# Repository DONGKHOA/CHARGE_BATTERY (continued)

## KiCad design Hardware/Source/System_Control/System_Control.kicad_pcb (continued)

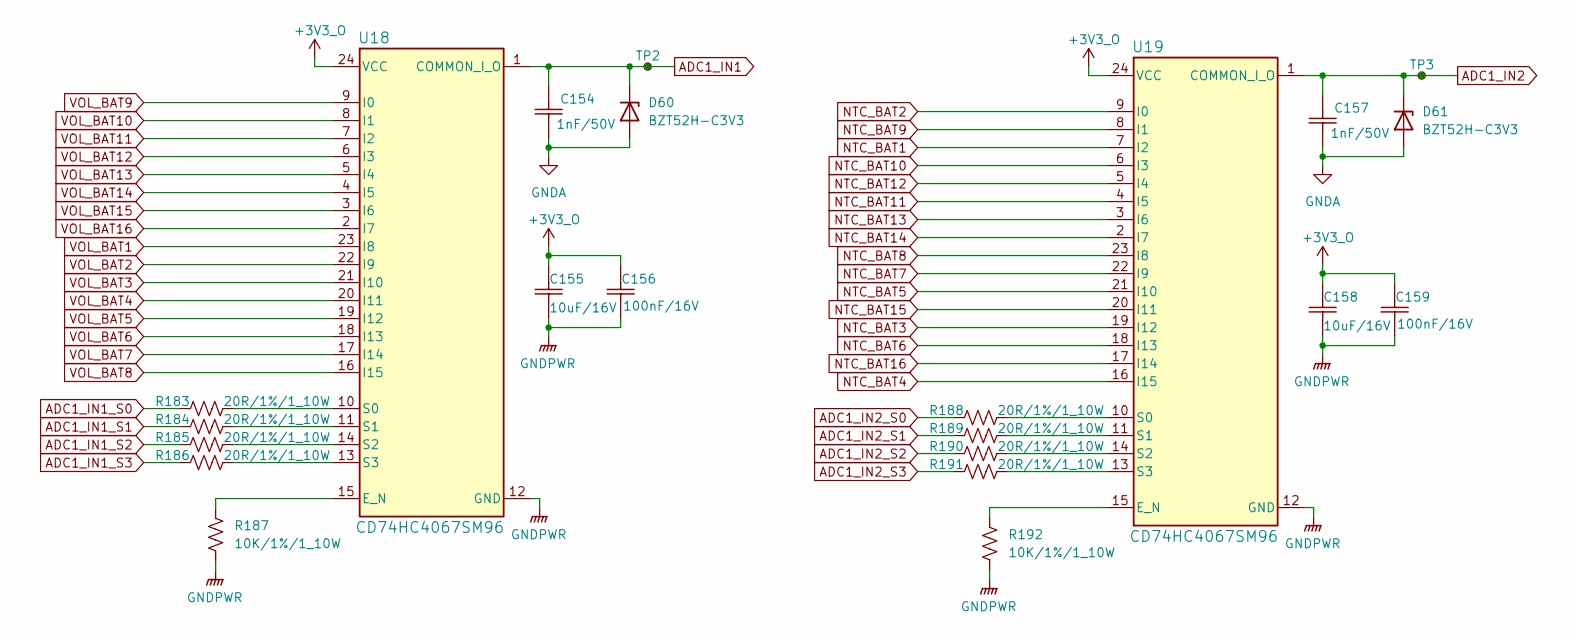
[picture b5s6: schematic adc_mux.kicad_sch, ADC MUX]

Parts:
C154, C157: 1nF/50V; Ceramic_Cap_0603
C155, C158: 10uF/16V; Ceramic_Cap_0603
C156, C159: 100nF/16V; Ceramic_Cap_0603
D60, D61: BZT52H-C3V3; Diode_Zener_BZT52H
R183, R184, R185, R186, R188, R189, R190, R191: 20R/1%/1_10W; Res_0603
R187, R192: 10K/1%/1_10W; Res_0603
TP2, TP3: TestPoint_Small; TestPoint_Pad_D1.0mm
U18, U19: CD74HC4067SM96; SOIC-24

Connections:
+3V3_O: C155.2, C156.2, C158.2, C159.2, U18.24 (VCC), U19.24 (VCC); also elsewhere on the board
ADC1_IN1: C154.2, D60.1 (K), TP2.1, U18.1 (COMMON_I_O); also elsewhere on the board
ADC1_IN1_S0: R183.1; also elsewhere on the board
ADC1_IN1_S1: R184.1; also elsewhere on the board
ADC1_IN1_S2: R185.1; also elsewhere on the board
ADC1_IN1_S3: R186.1; also elsewhere on the board
ADC1_IN2: C157.2, D61.1 (K), TP3.1, U19.1 (COMMON_I_O); also elsewhere on the board
ADC1_IN2_S0: R188.1; also elsewhere on the board
ADC1_IN2_S1: R189.1; also elsewhere on the board
ADC1_IN2_S2: R190.1; also elsewhere on the board
ADC1_IN2_S3: R191.1; also elsewhere on the board
GNDA: C154.1, C155.1, C156.1, C157.1, C158.1, C159.1, D60.2 (A), D61.2 (A), R187.1, R192.1, U18.12 (GND), U19.12 (GND); also elsewhere on the board
NTC_BAT1: U19.7 (I2); also elsewhere on the board
NTC_BAT2: U19.9 (I0); also elsewhere on the board
NTC_BAT3: U19.19 (I12); also elsewhere on the board
NTC_BAT4: U19.16 (I15); also elsewhere on the board
NTC_BAT5: U19.21 (I10); also elsewhere on the board
NTC_BAT6: U19.18 (I13); also elsewhere on the board
NTC_BAT7: U19.22 (I9); also elsewhere on the board
NTC_BAT8: U19.23 (I8); also elsewhere on the board
NTC_BAT9: U19.8 (I1); also elsewhere on the board
NTC_BAT10: U19.6 (I3); also elsewhere on the board
NTC_BAT11: U19.4 (I5); also elsewhere on the board
NTC_BAT12: U19.5 (I4); also elsewhere on the board
NTC_BAT13: U19.3 (I6); also elsewhere on the board
NTC_BAT14: U19.2 (I7); also elsewhere on the board
NTC_BAT15: U19.20 (I11); also elsewhere on the board
NTC_BAT16: U19.17 (I14); also elsewhere on the board
unnamed: R187.2, U18.15 (E_N)
unnamed: R183.2, U18.10 (S0)
unnamed: R184.2, U18.11 (S1)
unnamed: R185.2, U18.14 (S2)
unnamed: R186.2, U18.13 (S3)
unnamed: R192.2, U19.15 (E_N)
unnamed: R188.2, U19.10 (S0)
unnamed: R189.2, U19.11 (S1)
unnamed: R190.2, U19.14 (S2)
unnamed: R191.2, U19.13 (S3)
VOL_BAT1: U18.23 (I8); also elsewhere on the board
VOL_BAT2: U18.22 (I9); also elsewhere on the board
VOL_BAT3: U18.21 (I10); also elsewhere on the board
VOL_BAT4: U18.20 (I11); also elsewhere on the board
VOL_BAT5: U18.19 (I12); also elsewhere on the board
VOL_BAT6: U18.18 (I13); also elsewhere on the board
VOL_BAT7: U18.17 (I14); also elsewhere on the board
VOL_BAT8: U18.16 (I15); also elsewhere on the board
VOL_BAT9: U18.9 (I0); also elsewhere on the board
VOL_BAT10: U18.8 (I1); also elsewhere on the board
VOL_BAT11: U18.7 (I2); also elsewhere on the board
VOL_BAT12: U18.6 (I3); also elsewhere on the board
VOL_BAT13: U18.5 (I4); also elsewhere on the board
VOL_BAT14: U18.4 (I5); also elsewhere on the board
VOL_BAT15: U18.3 (I6); also elsewhere on the board
VOL_BAT16: U18.2 (I7); also elsewhere on the board

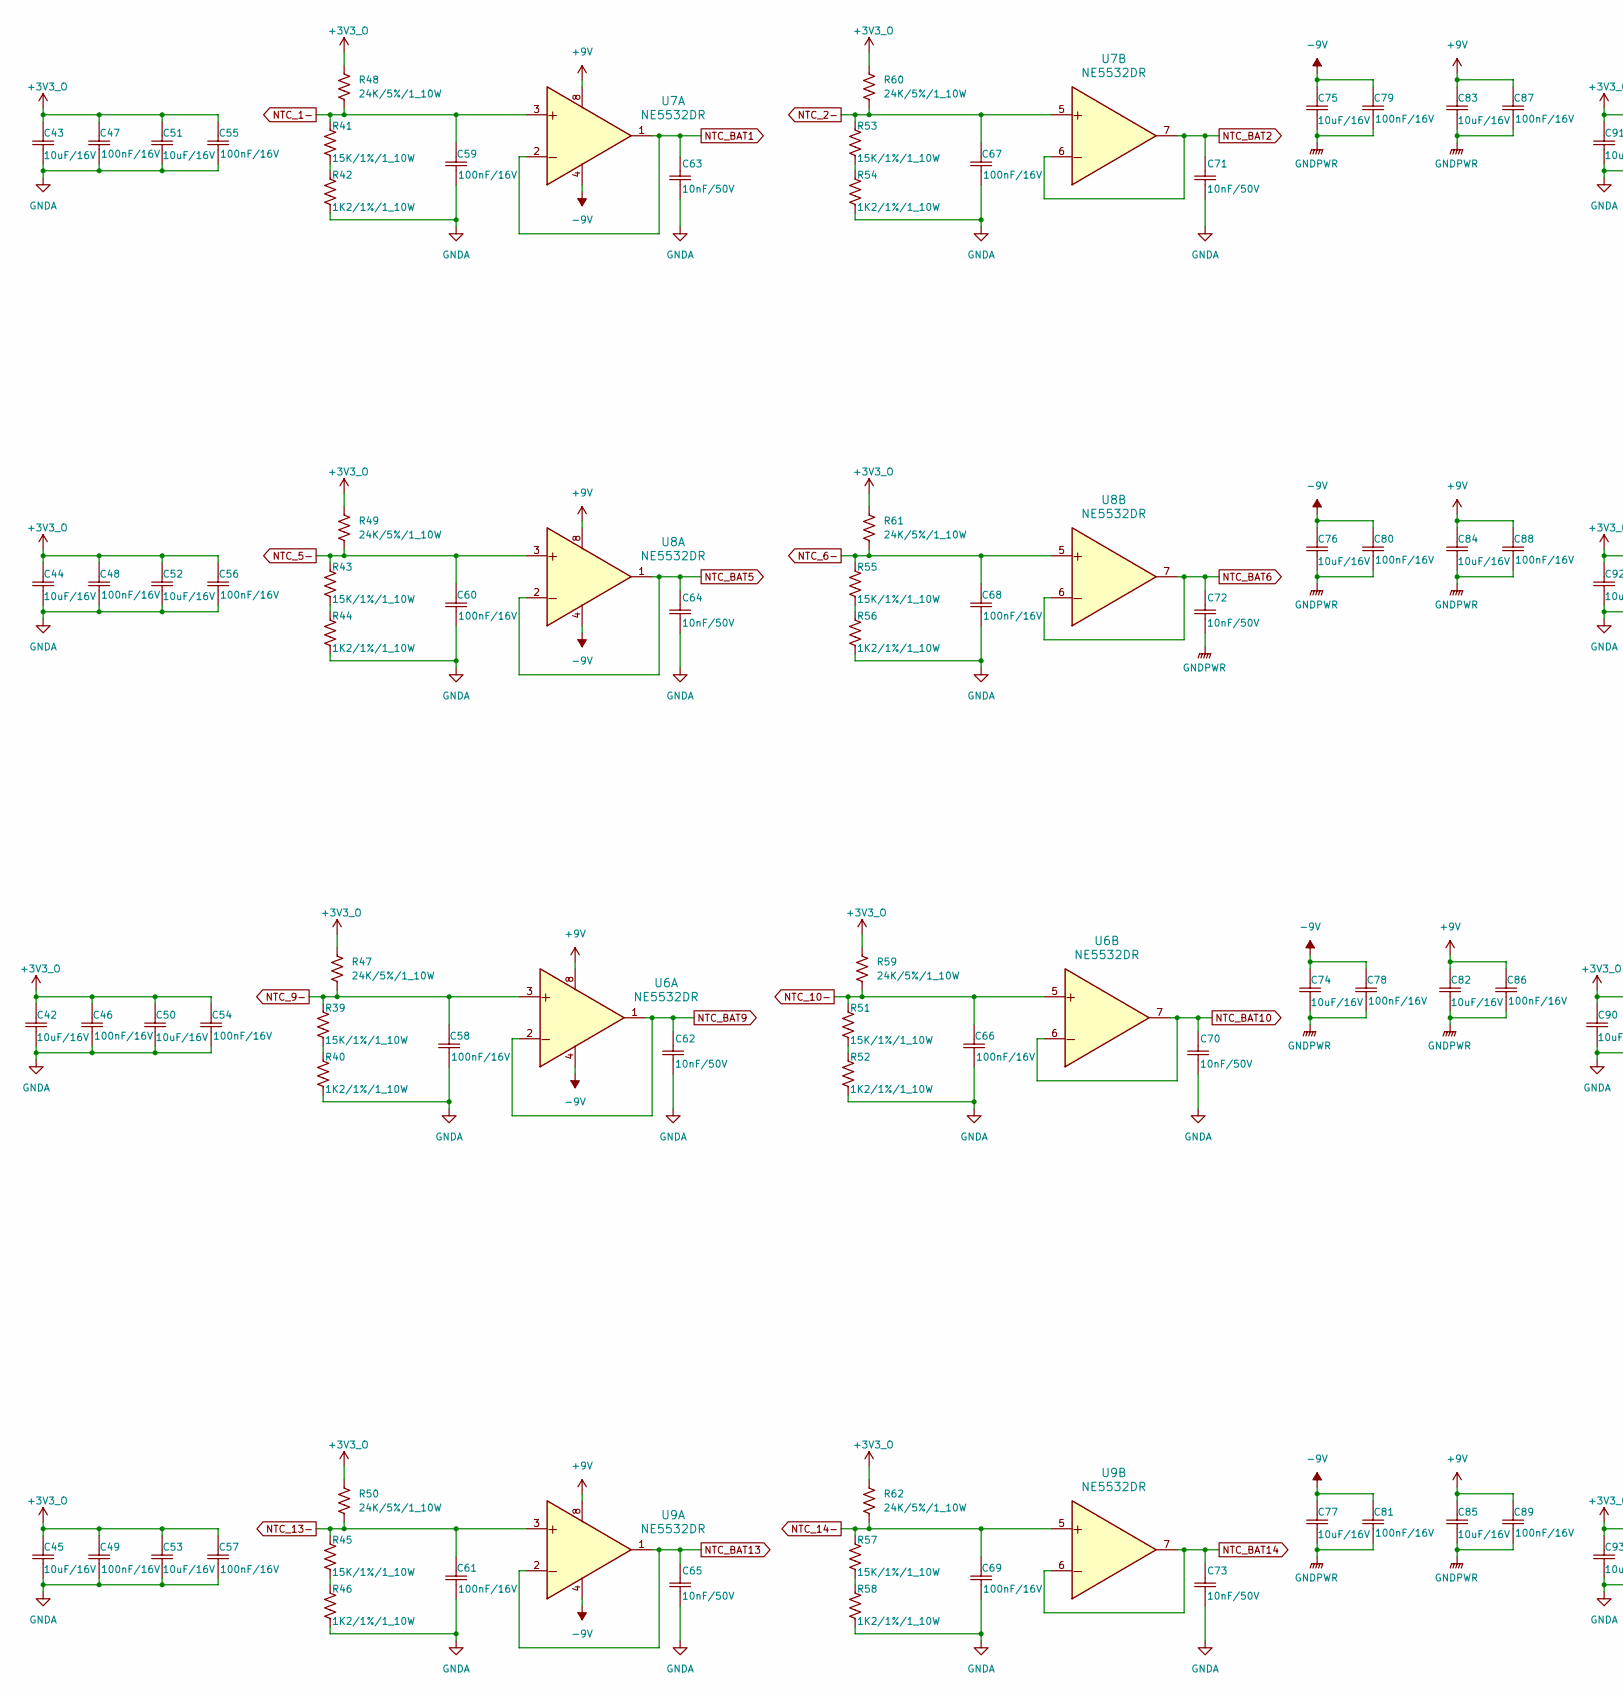
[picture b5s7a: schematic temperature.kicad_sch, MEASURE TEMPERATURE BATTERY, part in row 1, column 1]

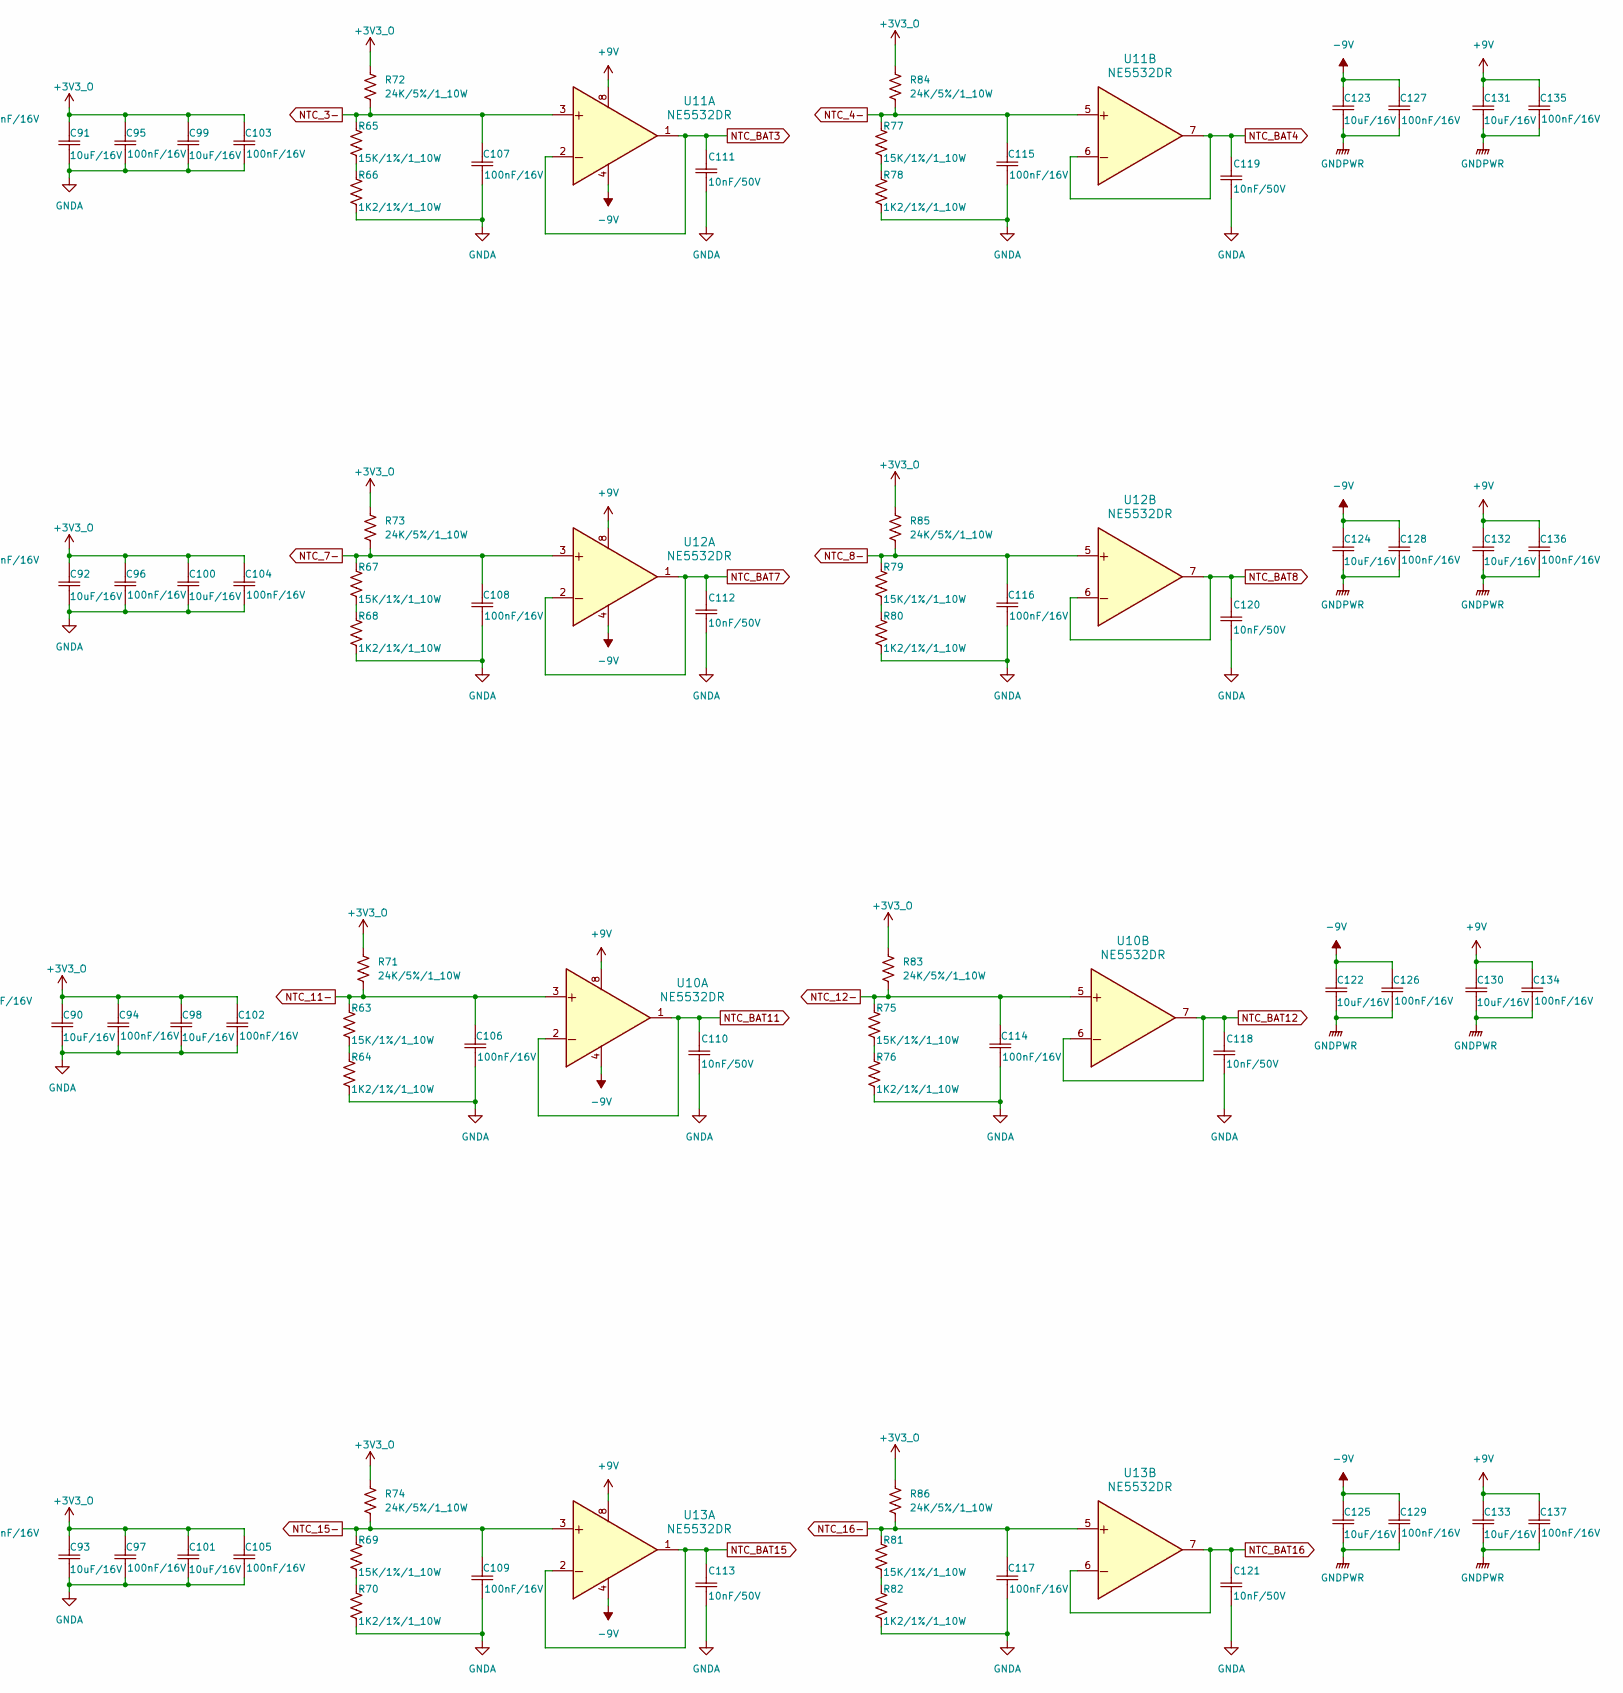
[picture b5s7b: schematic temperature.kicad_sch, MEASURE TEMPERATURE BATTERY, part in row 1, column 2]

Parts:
C42, C43, C44, C45, C50, C51, C52, C53, C74, C75, C76, C77, C82, C83, C84, C85, C90, C91, C92, C93, C98, C99, C100, C101, C122, C123, C124, C125, C130, C131, C132, C133: 10uF/16V; Ceramic_Cap_0603
C46, C47, C48, C49, C54, C55, C56, C57, C58, C59, C60, C61, C66, C67, C68, C69, C78, C79, C80, C81, C86, C87, C88, C89, C94, C95, C96, C97, C102, C103, C104, C105, C106, C107, C108, C109, C114, C115, C116, C117, C126, C127, C128, C129, C134, C135, C136, C137: 100nF/16V; Ceramic_Cap_0603
C62, C63, C64, C65, C70, C71, C72, C73, C110, C111, C112, C113, C118, C119, C120, C121: 10nF/50V; Ceramic_Cap_0603
R39, R41, R43, R45, R51, R53, R55, R57, R63, R65, R67, R69, R75, R77, R79, R81: 15K/1%/1_10W; Res_0603
R40, R42, R44, R46, R52, R54, R56, R58, R64, R66, R68, R70, R76, R78, R80, R82: 1K2/1%/1_10W; Res_0603
R47, R48, R49, R50, R59, R60, R61, R62, R71, R72, R73, R74, R83, R84, R85, R86: 24K/5%/1_10W; Res_0603
U6, U7, U8, U9, U10, U11, U12, U13: NE5532DR; SOIC-8

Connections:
+3V3_O: C42.2, C43.2, C44.2, C45.2, C46.2, C47.2, C48.2, C49.2, C50.2, C51.2, C52.2, C53.2, C54.2, C55.2, C56.2, C57.2, C90.2, C91.2, C92.2, C93.2, C94.2, C95.2, C96.2, C97.2, C98.2, C99.2, C100.2, C101.2, C102.2, C103.2, C104.2, C105.2, R47.2, R48.2, R49.2, R50.2, R59.2, R60.2, R61.2, R62.2, R71.2, R72.2, R73.2, R74.2, R83.2, R84.2, R85.2, R86.2; also elsewhere on the board
+9V: C82.2, C83.2, C84.2, C85.2, C86.2, C87.2, C88.2, C89.2, C130.2, C131.2, C132.2, C133.2, C134.2, C135.2, C136.2, C137.2, U6.8 (+), U7.8 (+), U8.8 (+), U9.8 (+), U10.8 (+), U11.8 (+), U12.8 (+), U13.8 (+); also elsewhere on the board
-9V: C74.2, C75.2, C76.2, C77.2, C78.2, C79.2, C80.2, C81.2, C122.2, C123.2, C124.2, C125.2, C126.2, C127.2, C128.2, C129.2, U6.4 (-), U7.4 (-), U8.4 (-), U9.4 (-), U10.4 (-), U11.4 (-), U12.4 (-), U13.4 (-); also elsewhere on the board
GNDA: C42.1, C43.1, C44.1, C45.1, C46.1, C47.1, C48.1, C49.1, C50.1, C51.1, C52.1, C53.1, C54.1, C55.1, C56.1, C57.1, C58.1, C59.1, C60.1, C61.1, C62.1, C63.1, C64.1, C65.1, C66.1, C67.1, C68.1, C69.1, C70.1, C71.1, C72.1, C73.1, C74.1, C75.1, C76.1, C77.1, C78.1, C79.1, C80.1, C81.1, C82.1, C83.1, C84.1, C85.1, C86.1, C87.1, C88.1, C89.1, C90.1, C91.1, C92.1, C93.1, C94.1, C95.1, C96.1, C97.1, C98.1, C99.1, C100.1, C101.1, C102.1, C103.1, C104.1, C105.1, C106.1, C107.1, C108.1, C109.1, C110.1, C111.1, C112.1, C113.1, C114.1, C115.1, C116.1, C117.1, C118.1, C119.1, C120.1, C121.1, C122.1, C123.1, C124.1, C125.1, C126.1, C127.1, C128.1, C129.1, C130.1, C131.1, C132.1, C133.1, C134.1, C135.1, C136.1, C137.1, R40.1, R42.1, R44.1, R46.1, R52.1, R54.1, R56.1, R58.1, R64.1, R66.1, R68.1, R70.1, R76.1, R78.1, R80.1, R82.1; also elsewhere on the board
NTC_1-: C59.2, R41.2, R48.1, U7.3 (1IN+); also elsewhere on the board
NTC_2-: C67.2, R53.2, R60.1, U7.5 (2IN+); also elsewhere on the board
NTC_3-: C107.2, R65.2, R72.1, U11.3 (1IN+); also elsewhere on the board
NTC_4-: C115.2, R77.2, R84.1, U11.5 (2IN+); also elsewhere on the board
NTC_5-: C60.2, R43.2, R49.1, U8.3 (1IN+); also elsewhere on the board
NTC_6-: C68.2, R55.2, R61.1, U8.5 (2IN+); also elsewhere on the board
NTC_7-: C108.2, R67.2, R73.1, U12.3 (1IN+); also elsewhere on the board
NTC_8-: C116.2, R79.2, R85.1, U12.5 (2IN+); also elsewhere on the board
NTC_9-: C58.2, R39.2, R47.1, U6.3 (1IN+); also elsewhere on the board
NTC_10-: C66.2, R51.2, R59.1, U6.5 (2IN+); also elsewhere on the board
NTC_11-: C106.2, R63.2, R71.1, U10.3 (1IN+); also elsewhere on the board
NTC_12-: C114.2, R75.2, R83.1, U10.5 (2IN+); also elsewhere on the board
NTC_13-: C61.2, R45.2, R50.1, U9.3 (1IN+); also elsewhere on the board
NTC_14-: C69.2, R57.2, R62.1, U9.5 (2IN+); also elsewhere on the board
NTC_15-: C109.2, R69.2, R74.1, U13.3 (1IN+); also elsewhere on the board
NTC_16-: C117.2, R81.2, R86.1, U13.5 (2IN+); also elsewhere on the board
NTC_BAT1: C63.2, U7.1 (1OUT), U7.2 (1IN-); also elsewhere on the board
NTC_BAT2: C71.2, U7.6 (2IN-), U7.7 (2OUT); also elsewhere on the board
NTC_BAT3: C111.2, U11.1 (1OUT), U11.2 (1IN-); also elsewhere on the board
NTC_BAT4: C119.2, U11.6 (2IN-), U11.7 (2OUT); also elsewhere on the board
NTC_BAT5: C64.2, U8.1 (1OUT), U8.2 (1IN-); also elsewhere on the board
NTC_BAT6: C72.2, U8.6 (2IN-), U8.7 (2OUT); also elsewhere on the board
NTC_BAT7: C112.2, U12.1 (1OUT), U12.2 (1IN-); also elsewhere on the board
NTC_BAT8: C120.2, U12.6 (2IN-), U12.7 (2OUT); also elsewhere on the board
NTC_BAT9: C62.2, U6.1 (1OUT), U6.2 (1IN-); also elsewhere on the board
NTC_BAT10: C70.2, U6.6 (2IN-), U6.7 (2OUT); also elsewhere on the board
NTC_BAT11: C110.2, U10.1 (1OUT), U10.2 (1IN-); also elsewhere on the board
NTC_BAT12: C118.2, U10.6 (2IN-), U10.7 (2OUT); also elsewhere on the board
NTC_BAT13: C65.2, U9.1 (1OUT), U9.2 (1IN-); also elsewhere on the board
NTC_BAT14: C73.2, U9.6 (2IN-), U9.7 (2OUT); also elsewhere on the board
NTC_BAT15: C113.2, U13.1 (1OUT), U13.2 (1IN-); also elsewhere on the board
NTC_BAT16: C121.2, U13.6 (2IN-), U13.7 (2OUT); also elsewhere on the board
unnamed: R39.1, R40.2
unnamed: R41.1, R42.2
unnamed: R43.1, R44.2
unnamed: R45.1, R46.2
unnamed: R51.1, R52.2
unnamed: R53.1, R54.2
unnamed: R55.1, R56.2
unnamed: R57.1, R58.2
unnamed: R63.1, R64.2
unnamed: R65.1, R66.2
unnamed: R67.1, R68.2
unnamed: R69.1, R70.2
unnamed: R75.1, R76.2
unnamed: R77.1, R78.2
unnamed: R79.1, R80.2
unnamed: R81.1, R82.2

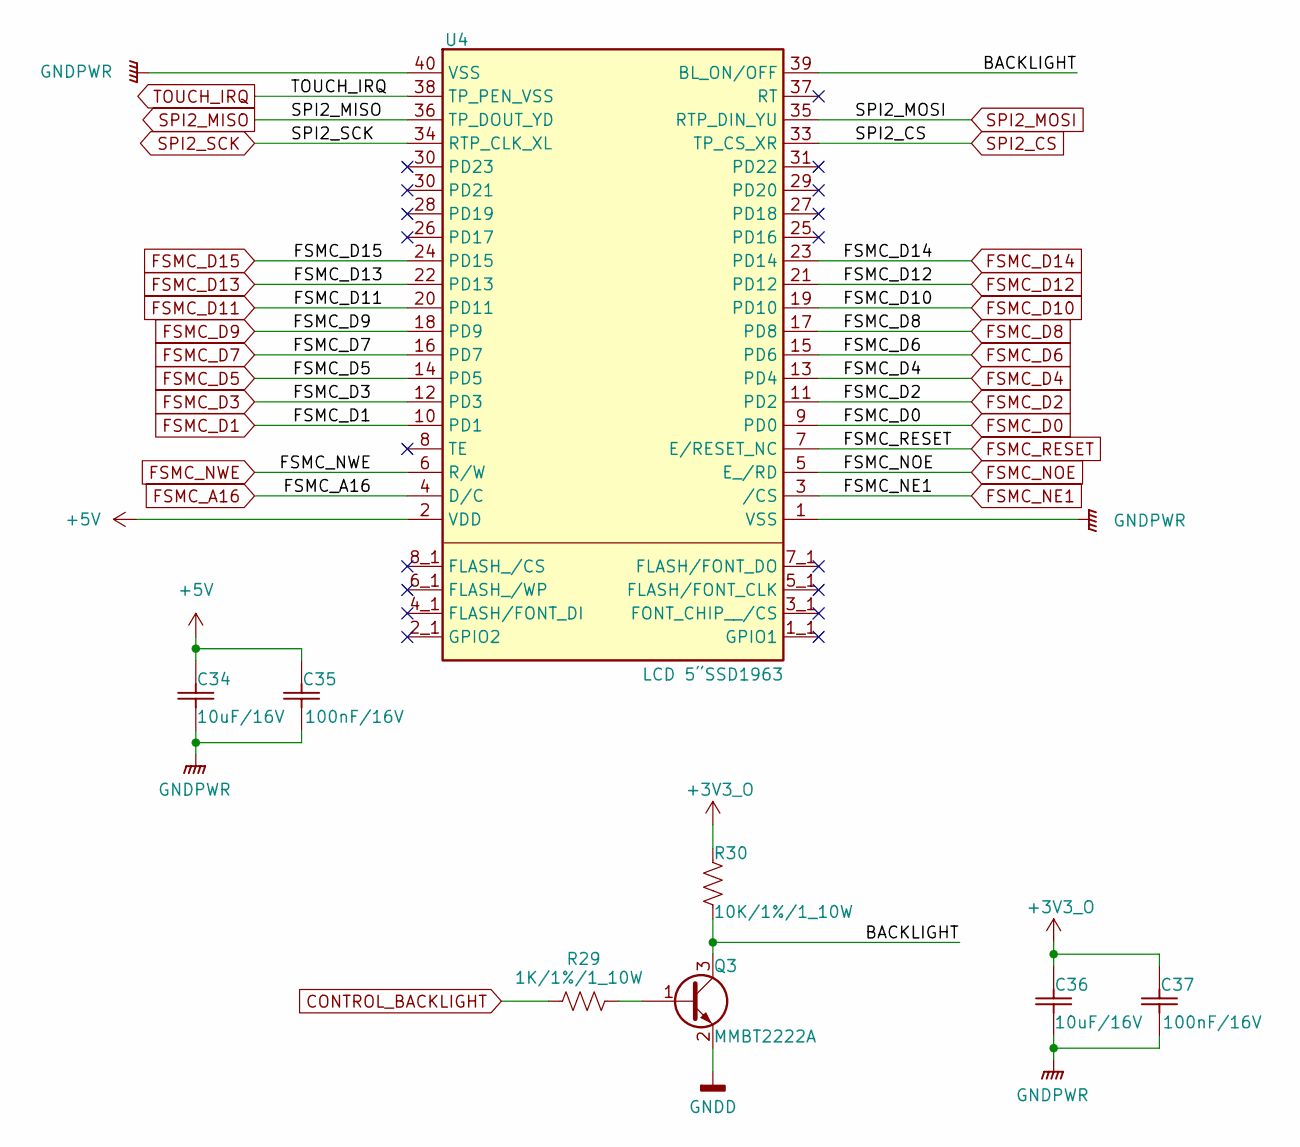
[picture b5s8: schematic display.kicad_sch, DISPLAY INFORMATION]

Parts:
C34, C36: 10uF/16V; Ceramic_Cap_0603
C35, C37: 100nF/16V; Ceramic_Cap_0603
Q3: MMBT2222A; SOT23
R29: 1K/1%/1_10W; Res_0603
R30: 10K/1%/1_10W; Res_0603
U4: LCD 5“SSD1963; LCD 5“SSD1963 TFT Module

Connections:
+3V3_O: C36.2, C37.2, R30.2; also elsewhere on the board
+5V: C34.2, C35.2, U4.2 (VDD); also elsewhere on the board
/DISPLAY/BACKLIGHT: Q3.3 (C), R30.1, U4.39 (BL_ON/OFF)
CONTROL_BACKLIGHT: R29.1; also elsewhere on the board
FSMC_A16: U4.4 (D/C); also elsewhere on the board
FSMC_D0: U4.9 (PD0); also elsewhere on the board
FSMC_D1: U4.10 (PD1); also elsewhere on the board
FSMC_D2: U4.11 (PD2); also elsewhere on the board
FSMC_D3: U4.12 (PD3); also elsewhere on the board
FSMC_D4: U4.13 (PD4); also elsewhere on the board
FSMC_D5: U4.14 (PD5); also elsewhere on the board
FSMC_D6: U4.15 (PD6); also elsewhere on the board
FSMC_D7: U4.16 (PD7); also elsewhere on the board
FSMC_D8: U4.17 (PD8); also elsewhere on the board
FSMC_D9: U4.18 (PD9); also elsewhere on the board
FSMC_D10: U4.19 (PD10); also elsewhere on the board
FSMC_D11: U4.20 (PD11); also elsewhere on the board
FSMC_D12: U4.21 (PD12); also elsewhere on the board
FSMC_D13: U4.22 (PD13); also elsewhere on the board
FSMC_D14: U4.23 (PD14); also elsewhere on the board
FSMC_D15: U4.24 (PD15); also elsewhere on the board
FSMC_NE1: U4.3 (/CS); also elsewhere on the board
FSMC_NOE: U4.5 (E_/RD); also elsewhere on the board
FSMC_NWE: U4.6 (R/W); also elsewhere on the board
FSMC_RESET: U4.7 (E/RESET_NC); also elsewhere on the board
GNDA: C34.1, C35.1, C36.1, C37.1, Q3.2 (E), U4.1 (VSS), U4.40 (VSS); also elsewhere on the board
unnamed: Q3.1 (B), R29.2
SPI2_CS: U4.33 (TP_CS_XR); also elsewhere on the board
SPI2_MISO: U4.36 (TP_DOUT_YD); also elsewhere on the board
SPI2_MOSI: U4.35 (RTP_DIN_YU); also elsewhere on the board
SPI2_SCK: U4.34 (RTP_CLK_XL); also elsewhere on the board
TOUCH_IRQ: U4.38 (TP_PEN_VSS); also elsewhere on the board

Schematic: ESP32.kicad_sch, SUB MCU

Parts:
C11, C14: 10uF/16V; Ceramic_Cap_0603
C12, C13, C15, C16, C17: 100nF/16V; Ceramic_Cap_0603
D6: SMF05C; SOT-363
D7, D8: LED_0805
J2: USB_B_Micro; USB_Micro-B_Wuerth_629105150521
Q1, Q2: MMBT2222A; SOT23
R6, R7: 1K/1%/1_10W; Res_0603
R8, R9: 20R/1%/1_10W; Res_0603
R10, R11, R13, R14: 20R/5%/1_16W; Res_0402
R12, R15, R16, R17, R18: 10K/1%/1_10W; Res_0603
SW1, SW2: SW_Push; SW_SMD
U1: ESP32-WROOM-32U
U2: CH340C; SOIC-16_3.9x9.9mm_P1.27mm

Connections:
+5V: C14.2, C17.2, U2.16 (VCC); also elsewhere on the board
/ESP32/DIR: Q2.2 (E), R13.2, R17.1
/ESP32/D_N: D6.6, J2.2 (D-), R9.1
/ESP32/D_P: D6.1, J2.3 (D+), R8.1
/ESP32/EN: C16.2, Q1.3 (C), R16.1, SW2.2, U1.3 (EN)
/ESP32/FLASH: C15.2, Q2.3 (C), R15.1, SW1.2, U1.25 (IO0)
/ESP32/LED_STATUS: D8.2 (A), U1.33 (IO21)
/ESP32/LED_TEST: D7.2 (A), U1.31 (IO19)
/ESP32/RTS: Q1.2 (E), R14.2, R18.1
/ESP32/U_N: R9.2, U2.6 (UD-)
/ESP32/U_P: R8.2, U2.5 (UD+)
CONTROL_BOOT0: U1.16 (IO13); also elsewhere on the board
CONTROL_BOOT1: U1.14 (IO12); also elsewhere on the board
ESP_RX: U1.23 (IO15); also elsewhere on the board
ESP_TX: U1.28 (IO17); also elsewhere on the board
GNDA: C11.1, C12.1, C13.2, C14.1, C15.1, C16.1, C17.1, D6.2, J2.5 (GND), J2.6 (Shield), R6.2, R7.2, SW1.1, SW2.1, U1.1 (GND), U1.15 (GND), U1.38 (GND), U1.39 (GND), U2.1 (GND); also elsewhere on the board
unnamed: D7.1 (K), R6.1
unnamed: D8.1 (K), R7.1
unnamed: Q1.1 (B), R17.2
unnamed: Q2.1 (B), R18.2
unnamed: R12.2, U1.27 (IO16)
unnamed: R11.1, U1.34 (RXD0/IO3)
unnamed: R10.1, U1.35 (TXD0/IO1)
unnamed: C13.1, U2.4 (V3)
unnamed: R13.1, U2.13 (~DTR)
unnamed: R14.1, U2.14 (~RTS)
U0_N: R11.2, U2.2 (TXD)
U0_P: R10.2, U2.3 (RXD)
VBAT: C11.2, C12.2, R12.1, R15.2, R16.2, U1.2 (VDD); also elsewhere on the board

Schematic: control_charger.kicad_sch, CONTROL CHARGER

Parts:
Q21, Q24: MMBT2222A; SOT23
Q22, Q23: SQJ211ELP-T1_GE3; PowerPAK SO-8
R193, R200: 1K/1%/1_10W; Res_0603
R194, R195, R198, R199: 10K/1%/1_10W; Res_0603
R196, R197: 30K/1%/1_10W; Res_0603
TP4: TestPoint_Small; TestPoint_Pad_D1.0mm

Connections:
BAT_BAL_1: Q23.1 (S), Q23.2 (S), Q23.3 (S), R199.2; also elsewhere on the board
CHARGE: R193.1; also elsewhere on the board
DISCHARGE: R200.2; also elsewhere on the board
GNDA: Q21.2 (E), Q24.2 (E), R195.1, R198.1; also elsewhere on the board
unnamed: Q21.1 (B), R193.2, R195.2
unnamed: Q21.3 (C), R196.1
unnamed: Q22.5 (D), Q23.5 (D), TP4.1
unnamed: Q22.4 (G), R194.1, R196.2
unnamed: Q23.4 (G), R197.2, R199.1
unnamed: Q24.1 (B), R198.2, R200.1
unnamed: Q24.3 (C), R197.1
V_CHARGER_P: Q22.1 (S), Q22.2 (S), Q22.3 (S), R194.2; also elsewhere on the board

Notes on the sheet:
51.2V

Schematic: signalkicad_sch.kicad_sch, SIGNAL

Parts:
C38, C40: 10uF/16V; Ceramic_Cap_0603
C39, C41: 100nF/16V; Ceramic_Cap_0603
D11: SMF05C; SOT-363
Q4: MMBT2222A; SOT23
R31, R32, R33, R37, R38: 10K/1%/1_10W; Res_0603
R34, R35: 20R/1%/1_10W; Res_0603
R36: 120/1%/1_10W; Res_0603
U5: MAX485CSA; SOIC-8

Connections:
+5V: C40.2, C41.2, R38.2, U5.8 (VCC); also elsewhere on the board
GNDA: C38.1, C39.1, C40.1, C41.1, D11.2, Q4.2 (E), R37.2, U5.5 (GND); also elsewhere on the board
unnamed: Q4.1 (B), R33.2
unnamed: Q4.3 (C), R32.2, U5.2 (*RE), U5.3 (DE)
unnamed: R35.2, U5.4 (DI)
unnamed: R34.2, U5.1 (RO)
RS485_CONTROL: R31.1, R33.1; also elsewhere on the board
RS485_N: D11.4, R36.2, R37.1, U5.7 (B); also elsewhere on the board
RS485_P: D11.3, R36.1, R38.1, U5.6 (A); also elsewhere on the board
UART4_RX: R34.1; also elsewhere on the board
UART4_TX: R35.1; also elsewhere on the board
VBAT: C38.2, C39.2, R31.2, R32.1; also elsewhere on the board

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
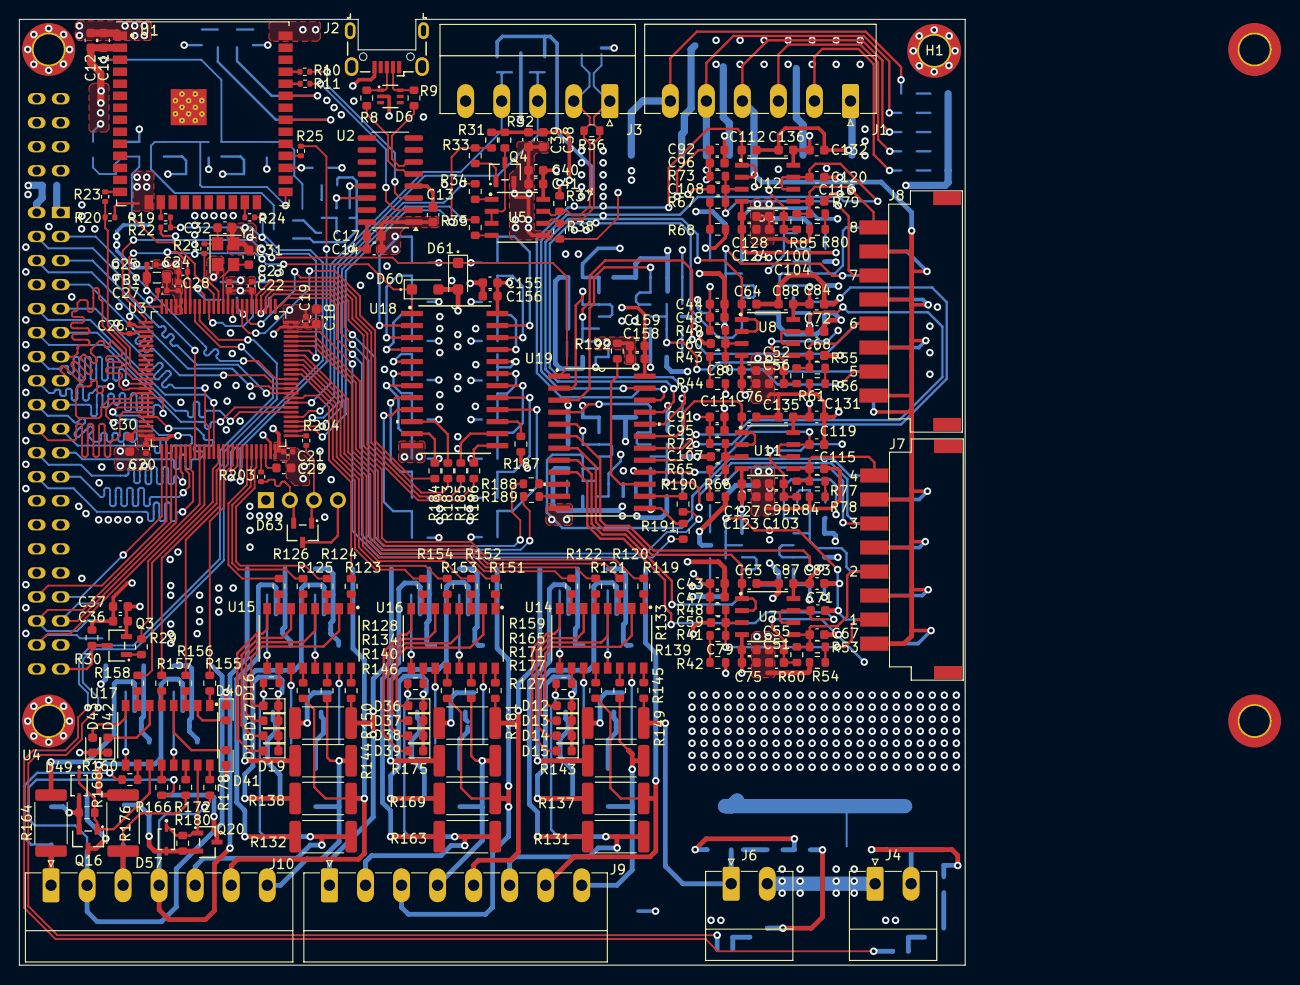
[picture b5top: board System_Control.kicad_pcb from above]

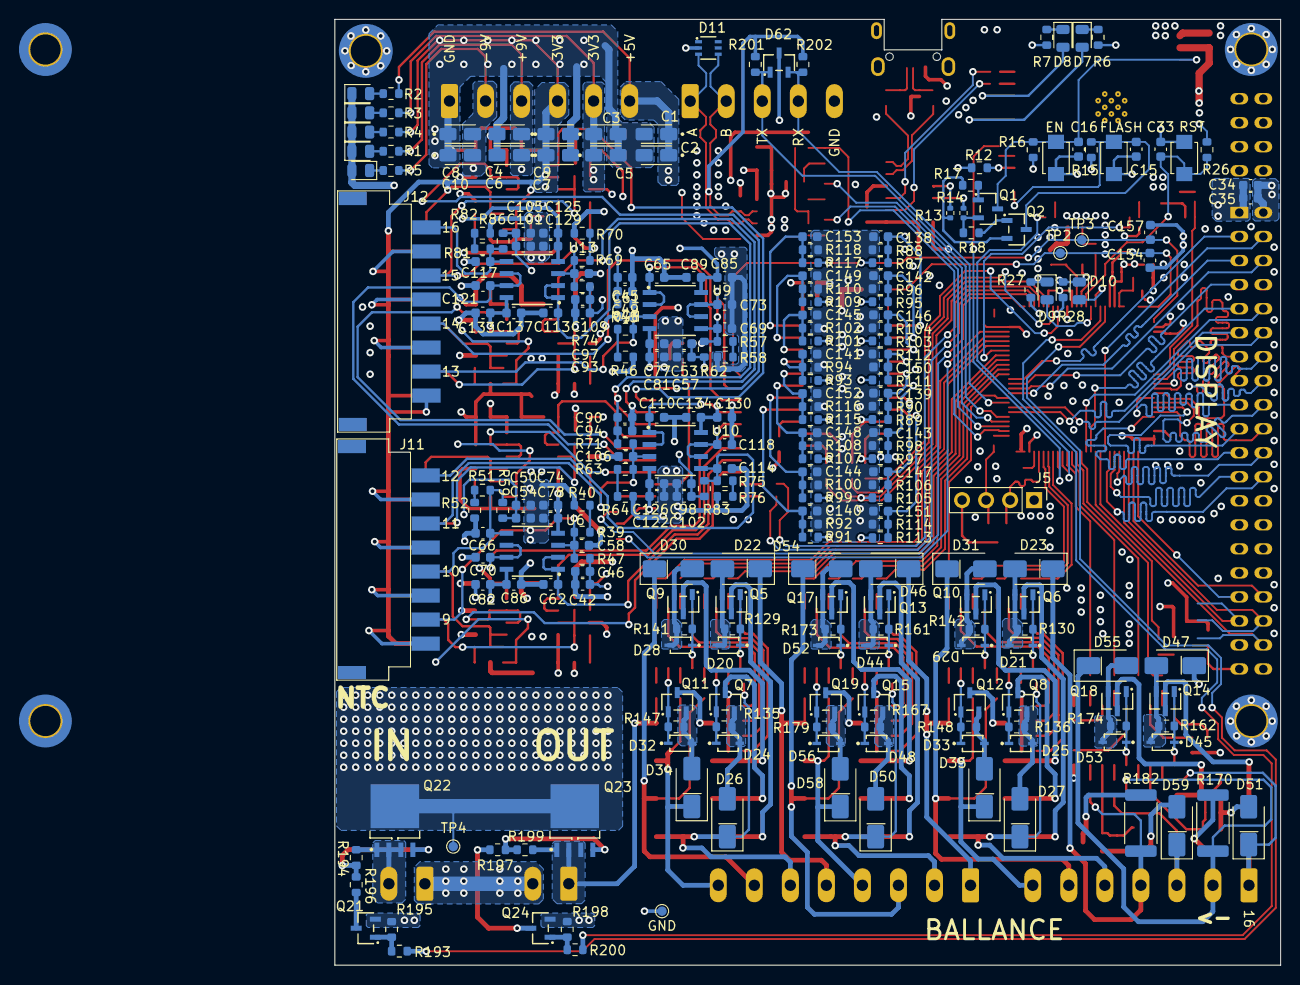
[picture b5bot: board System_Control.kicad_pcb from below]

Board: 4 copper layers, 100.0 x 100.0 mm, 491 parts (255 on the bottom side), 318 nets.

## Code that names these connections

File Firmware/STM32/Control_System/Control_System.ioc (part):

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Mcu.Name=STM32F407V(E-G)Tx
Mcu.Package=LQFP100
Mcu.UserName=STM32F407VETx
PA10.Mode=Asynchronous
PA10.Signal=USART1_RX
PA11.GPIOParameters=GPIO_Label
PA11.GPIO_Label=BAL_11
PA11.Signal=GPIO_Output
PA12.GPIOParameters=GPIO_Label
PA12.GPIO_Label=BAL_10
PA12.Signal=GPIO_Output
PA13.Mode=Serial_Wire
PA13.Signal=SYS_JTMS-SWDIO
PA14.Mode=Serial_Wire
PA14.Signal=SYS_JTCK-SWCLK
PA15.GPIOParameters=GPIO_Label
PA15.GPIO_Label=RS485_CONTROL
PA15.Signal=GPIO_Output
PA2.Signal=ADCx_IN2
PA3.Signal=ADCx_IN3
PA8.GPIOParameters=GPIO_Label
PA8.GPIO_Label=BAL_12
PA8.Signal=GPIO_Output
PA9.Mode=Asynchronous
PA9.Signal=USART1_TX
PB12.Mode=NSS_Signal_Hard_Output
PB12.Signal=SPI2_NSS
PB13.Mode=Full_Duplex_Master
PB13.Signal=SPI2_SCK
PB14.Mode=Full_Duplex_Master
PB14.Signal=SPI2_MISO
PB15.Mode=Full_Duplex_Master
PB15.Signal=SPI2_MOSI
PB3.GPIOParameters=GPIO_Label
PB3.GPIO_Label=BAL_8
PB3.Signal=GPIO_Output
PB4.GPIOParameters=GPIO_Label
PB4.GPIO_Label=BAL_7
PB4.Signal=GPIO_Output
PB5.GPIOParameters=GPIO_Label
PB5.GPIO_Label=BAL_6
PB5.Signal=GPIO_Output
PB6.GPIOParameters=GPIO_Label
PB6.GPIO_Label=BAL_5
PB6.Signal=GPIO_Output
PB7.GPIOParameters=GPIO_Label
PB7.GPIO_Label=BAL_4
PB7.Signal=GPIO_Output
PB8.GPIOParameters=GPIO_Label
PB8.GPIO_Label=BAL_3
PB8.Signal=GPIO_Output
PB9.GPIOParameters=GPIO_Label
PB9.GPIO_Label=BAL_2
PB9.Signal=GPIO_Output
PC0.GPIOParameters=GPIO_Label
PC0.GPIO_Label=LED_TEST
PC0.Signal=GPIO_Output
PC1.GPIOParameters=GPIO_Label
PC1.GPIO_Label=LED_STATUS
PC1.Signal=GPIO_Output
PC10.Mode=Asynchronous
PC10.Signal=UART4_TX
PC11.Mode=Asynchronous
PC11.Signal=UART4_RX
PC12.Mode=Asynchronous
PC12.Signal=UART5_TX
PC13-ANTI_TAMP.GPIOParameters=GPIO_Label
PC13-ANTI_TAMP.GPIO_Label=ADC1_IN1_S1
PC13-ANTI_TAMP.Signal=GPIO_Output
PC14-OSC32_IN.GPIOParameters=GPIO_Label
PC14-OSC32_IN.GPIO_Label=ADC1_IN1_S0
PC14-OSC32_IN.Signal=GPIO_Output
PC2.GPIOParameters=GPIO_Label
PC2.GPIO_Label=DISCHARGE
PC2.Signal=GPIO_Output
PC3.GPIOParameters=GPIO_Label
PC3.GPIO_Label=CHARGE
PC3.Signal=GPIO_Output
PC6.GPIOParameters=GPIO_Label
PC6.GPIO_Label=BAL_16
PC6.Signal=GPIO_Output
PC7.GPIOParameters=GPIO_Label
PC7.GPIO_Label=BAL_15
PC7.Signal=GPIO_Output
PC8.GPIOParameters=GPIO_Label
PC8.GPIO_Label=BAL_14
PC8.Signal=GPIO_Output
PC9.GPIOParameters=GPIO_Label
PC9.GPIO_Label=BAL_13
PC9.Signal=GPIO_Output
PD0.Mode=16b-d1
PD0.Signal=FSMC_D2
PD1.Mode=16b-d1
PD1.Signal=FSMC_D3
PD10.Mode=16b-d1
PD10.Signal=FSMC_D15
PD11.Mode=A16_1
PD11.Signal=FSMC_A16
PD12.GPIOParameters=GPIO_Label
PD12.GPIO_Label=TOUCH_IRQ
PD12.Signal=GPIO_Input
PD13.GPIOParameters=GPIO_Label
PD13.GPIO_Label=CONTROL_BACKLIGHT
PD13.Signal=GPIO_Output
PD14.Mode=16b-d1
PD14.Signal=FSMC_D0
PD15.Mode=16b-d1
PD15.Signal=FSMC_D1
PD2.Mode=Asynchronous
PD2.Signal=UART5_RX
PD3.GPIOParameters=GPIO_Label
PD3.GPIO_Label=BAL_9
PD3.Signal=GPIO_Output
PD4.Mode=Lcd1
PD4.Signal=FSMC_NOE
PD5.Mode=Lcd1
PD5.Signal=FSMC_NWE
PD7.Mode=NorPsramChipSelect1_1
PD7.Signal=FSMC_NE1
PD8.Mode=16b-d1
PD8.Signal=FSMC_D13
PD9.Mode=16b-d1
PD9.Signal=FSMC_D14
PE0.GPIOParameters=GPIO_Label
PE0.GPIO_Label=BAL_1
PE0.Signal=GPIO_Output
PE1.GPIOParameters=GPIO_Label
PE1.GPIO_Label=ADC1_IN2_S3
PE1.Signal=GPIO_Output
PE10.Mode=16b-d1
PE10.Signal=FSMC_D7
PE11.Mode=16b-d1
PE11.Signal=FSMC_D8
PE12.Mode=16b-d1
PE12.Signal=FSMC_D9
PE13.Mode=16b-d1
PE13.Signal=FSMC_D10
PE14.Mode=16b-d1
PE14.Signal=FSMC_D11
PE15.Mode=16b-d1
PE15.Signal=FSMC_D12
PE2.GPIOParameters=GPIO_Label
PE2.GPIO_Label=ADC1_IN2_S2
PE2.Signal=GPIO_Output
PE3.GPIOParameters=GPIO_Label
PE3.GPIO_Label=ADC1_IN2_S1
PE3.Signal=GPIO_Output
PE4.GPIOParameters=GPIO_Label
PE4.GPIO_Label=ADC1_IN2_S0
PE4.Signal=GPIO_Output
PE5.GPIOParameters=GPIO_Label
PE5.GPIO_Label=ADC1_IN1_S3
PE5.Signal=GPIO_Output
PE6.GPIOParameters=GPIO_Label
PE6.GPIO_Label=ADC1_IN1_S2
PE6.Signal=GPIO_Output
PE7.Mode=16b-d1
PE7.Signal=FSMC_D4
PE8.Mode=16b-d1
PE8.Signal=FSMC_D5
PE9.Mode=16b-d1
PE9.Signal=FSMC_D6
PH0-OSC_IN.Mode=HSE-External-Oscillator
PH0-OSC_IN.Signal=RCC_OSC_IN
PH1-OSC_OUT.Mode=HSE-External-Oscillator
PH1-OSC_OUT.Signal=RCC_OSC_OUT
RCC.HSE_VALUE=25000000
RCC.SYSCLKFreq_VALUE=120000000
RCC.SYSCLKSource=RCC_SYSCLKSOURCE_PLLCLK
board=custom

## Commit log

2024-06-01 upload folder Project
2024-06-03 fea:stm32:update ioc
2024-06-05 Add Schematic
2024-06-05 ref:hardware:schematic example
2024-06-12 votri
2024-06-14 hardware: switch from altium to kicad
2024-06-20 document:PFC:upload document by Viet
2024-06-20 ran wifi_code
2024-06-22 deleted_wifi
2024-06-22 hardware:lib: update ucc, diode, choke
2024-06-23 hardware:sche:update PFC
2024-06-24 chen password vao cho trong thanh cong
2024-06-24 xong ham update wifi
2024-06-25 update lib hardware
2024-06-26 xong wifi
2024-06-27 update library
2024-06-27 upload structure hardware
2024-06-29 update library except inductor incompleted
2024-06-29 upload cmdline
2024-07-02 updated full library
2024-07-06 upload Control LLC stm32
2024-07-08 run_thingsboard
2024-07-08 finish_thingsboard_lib
2024-07-09 fea:upload project in stm32 folder
2024-07-11 update PFC schematic and library
2024-07-12 changed name function in Thingsboard Lib
2024-07-12 update function for LLC
2024-07-13 Update library 13_7_2024
2024-07-13 update library: res symbol, change grid to 50mil
2024-07-13 change schematic
2024-07-13 Update LLC
2024-07-13 update: schematic PFC
2024-07-13 Update LLC Schematic
2024-07-13 completed PFC
2024-07-13 lib:update function frequency convert pulse
2024-07-15 fea:BSP_LLC: updata uart driver, upload i2c driver
2024-07-15 update: library from require of Thang
2024-07-17 Add MCU Schematic, missing library components for MCU, not done
2024-07-17 update: library and fix the schematic from require of Viet but some point havenot been clarified including C8, C9, C11, R1, R10
2024-07-17 re-update: library and fix the schematic from require of Viet but some point havenot been clarified including C8, C9, C11, R1, R10
2024-07-18 schematic:updat PFC, main
2024-07-18 update PFC
2024-07-18 nothing change
2024-07-18 update: LLC
2024-07-18 update: PFC
2024-07-18 Update Schematic MCU, LLC
2024-07-22 hardware:sche: update schematic F4, F1
2024-07-23 fea:BSP, Mid: update pwm, Mid
2024-07-23 nothing changed
2024-07-23 Combine Sche in Source: PFC, LLC, F1, F4, ESP32
2024-07-24 update PFC 1200W
2024-07-24 update_PFC_1200W
2024-07-24 fix:Mid: fix search frequency and data FCP
2024-07-24 add PWM function
2024-07-24 nothing
2024-07-25 Hardware: Update PFC and Sheet Entry
2024-07-26 update control power
2024-07-26 update path library
2024-07-26 Update sche
2024-07-26 update firmware
2024-07-26 update vo tri
2024-07-26 Update ki la
2024-07-27 update PFC return 360W
2024-07-27 name:BSP, APP: update name function
2024-07-27 Update ADC convert Voltage function
2024-07-27 remove .metadata
2024-08-02 fea:llc:update
2024-08-03 Update:data_private - table_data_proces
2024-08-04 Update: Feedback Voltage
2024-08-07 Create 3 new folder: PFC&LLC, PowerSupply, SystemControl
2024-08-09 update: library
2024-08-23 Update Folder
2024-08-26 Create library Opto for LLC
2024-08-28 Update PCB PFC
2024-08-28 Voltage Protection added
2024-08-29 Push PFC & LLC sche
2024-08-29 update lib
2024-08-30 update diode symbol footprint
2024-08-30 update PESD2USB3UXT-QR
2024-08-30 update symbol
2024-08-30 Modify library components
2024-08-30 Modified Sche PFC in Temp Folder
2024-08-31 Removed 3D model
2024-09-01 upload LN2302LT1G lib
2024-09-01 update tantalum lib
2024-09-02 update footprint
2024-09-02 update res 100, fet balance"
2024-09-02 Update Toroidal Inductor Lib
2024-09-02 Update Lib and Sche PFC
2024-09-03 update sche control system
2024-09-03 Modified sche PFC & LLC and Annotated number components
2024-09-03 update lib ir2104spbf
2024-09-03 update lib ss54
2024-09-03 Modified PFC & LLC schematic
2024-09-04 Update PFC & LLC Sche
2024-09-10 update lib diode, ic control flyback
2024-09-11 update R shunt 100mOhm
2024-09-11 update res lib
2024-09-11 update flyback lib
2024-09-11 Update Sche PFC & LLC
2024-09-11 update lib flyback
2024-09-11 update lan 2 cai flyback lib
2024-09-12 Fix current measurement
2024-09-12 tuan update symbol
2024-09-12 update sche PSU
2024-09-12 update inductor CDRH104 1038-220
2024-09-12 update cap buck
2024-09-12 Update Sche Power
2024-09-12 Update Sche 12V Power
2024-09-12 update sche buck 12v
2024-09-12 Fix lib
2024-09-12 Chargepump
2024-09-12 fix GND2
2024-09-12 check PFC-LLC
2024-09-12 check Flyback
2024-09-13 update lib inductor
2024-09-13 Exported BOM PFC & LLC
2024-09-13 upload LVGL
2024-09-13 schematic: update connector charger board F4
2024-09-14 pcb,lib,sche: PFC, lib: update pcb PFC, lib
2024-09-14 nothing update
2024-09-15 uodate
2024-09-15 update lib PFC
2024-09-15 3d:lib:update 3d model heatsink
2024-09-15 layout PFC
2024-09-15 update lib lcd
2024-09-15 update pcb
2024-09-16 pull
2024-09-17 footprint:lib:update header xh2.54 8pin smd
2024-09-17 update new flyback lib
2024-09-18 pull lib
2024-09-19 update lib PSC
2024-09-19 Update Lib ER35 Transformer
2024-09-24 check
2024-09-25 Update PCB PFC&LLC
2024-09-27 Update Lib: Ceramic_cap_1812 100nF/1KV
2024-09-27 Update Lib: Res_50mR_1%_2512
2024-09-27 Update Lib: Res_100mR
2024-09-27 Update PFC&LLC
2024-09-29 update pcb flyback
2024-09-30 tuan uupdate lib
2024-09-30 pcb:system_control: update teardrop
2024-09-30 update de sua sche
2024-09-30 flyback 7V
2024-09-30 update flyback co 7V
2024-10-01 update lib flyback Choke
2024-10-01 lib:foot, sym: upload opamp iso, led 5
2024-10-01 update FLYBACK tt
2024-10-03 update flyback almost done
2024-10-03 PFC&LLC almost done
2024-10-05 pcb:bat_con:update pcb
2024-10-05 Update lib: Choke in PFC Circuit
2024-10-05 update bat
2024-10-06 Update Gerber Folder
2024-10-06 Exported BOM List 4 boards
2024-10-06 tuan update flyback gerber
2024-10-07 Update Battery Converter Project
2024-10-07 Export Gerber file except Powersupply
2024-10-07 update flyback pcb
2024-10-07 add logo BKU
2024-10-08 Check Gerber File
2024-10-08 bsp:control_LLC: update gpio
2024-10-08 bsp:control_System: update XPT2046
2024-10-12 format:.clang-format: update format
2024-10-12 update control LLC
2024-10-13 function: Update name function ring buffer in Control LLC
2024-10-16 update Control LLC state machine, status led, deadtime, enable tim3
2024-10-21 app, scheduler: app_check_input_voltage, scheduler: upload app_check_input voltage, update scheduler for task ASYNC
2024-10-23 update test
2024-11-02 update test, app
2024-11-03 update ver 2.0 PFC-LLC
2024-11-05 update FEEDBACK, AC
2024-11-07 update lib, LLC
2024-11-07 update schematic, pdf
2024-11-09 update test board
2024-11-09 update test board folder
2024-11-09 upload Test LLC, Test Measure AC Voltage
2024-11-12 update test gate driver
2024-11-13 Update Test Board:AC Voltage
2025-03-12 update project
2025-03-12 update path symbol and footprint
2025-03-24 update: Add the Darlington transistors to the relay controller circuits
2025-03-24 change name of Tuan from Tuan Ho to Pham Tuan
2025-03-24 update 123
2025-03-24 update 1234
2025-03-25 update path lib project
